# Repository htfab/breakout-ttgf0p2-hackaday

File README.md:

# Tiny Tapeout GF 0p2 Hackaday PCB

<!--&emsp;
-->

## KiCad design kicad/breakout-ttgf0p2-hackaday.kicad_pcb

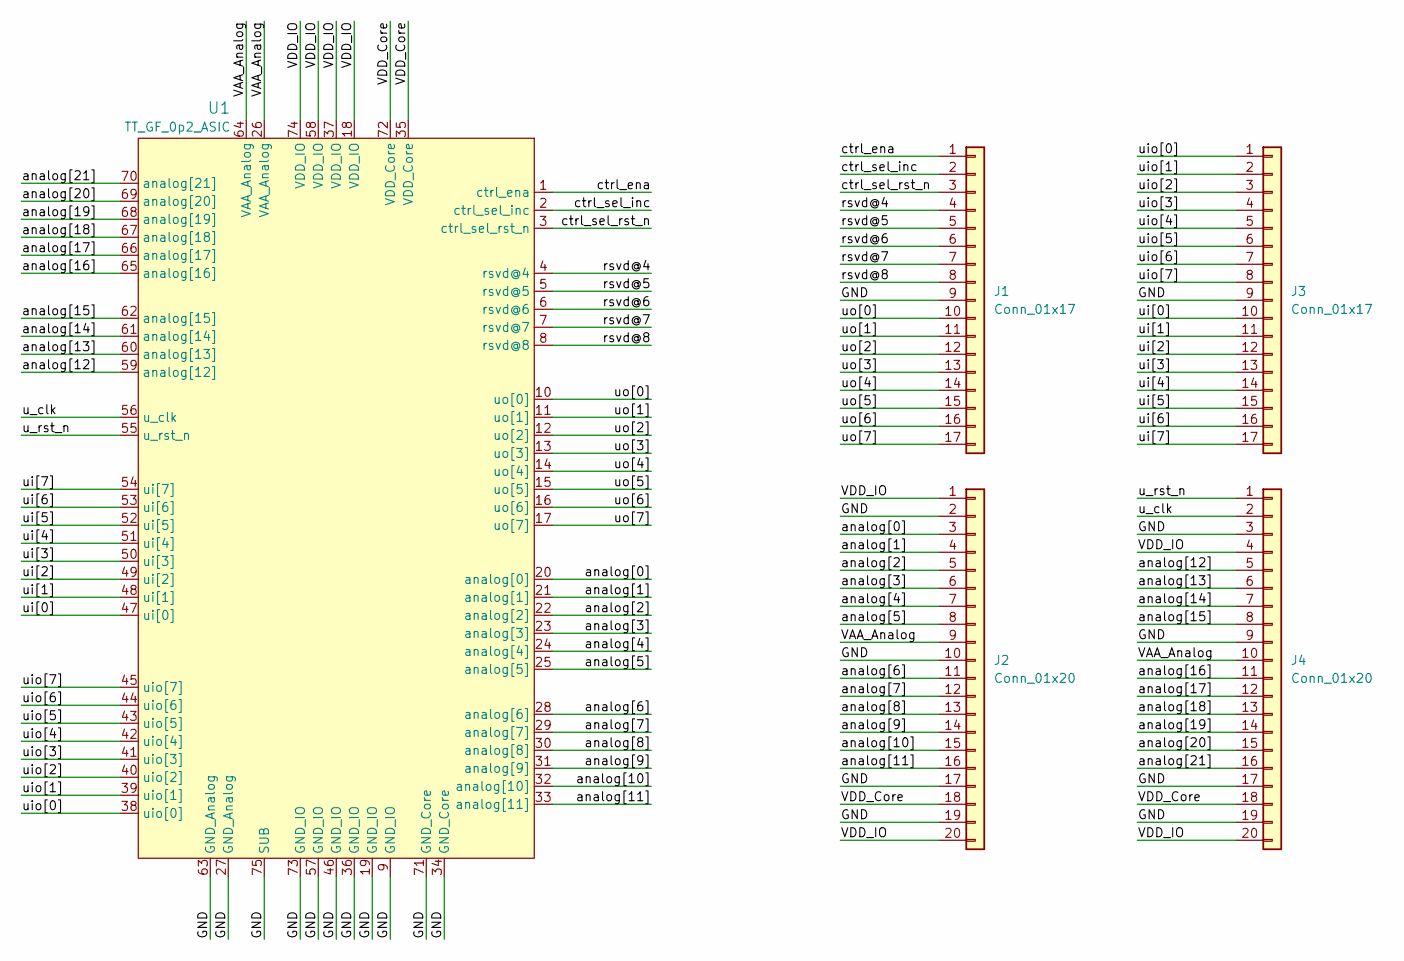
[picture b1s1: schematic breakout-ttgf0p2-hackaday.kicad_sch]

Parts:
J1, J3: Conn_01x17; PinHeader_1x17_P2.54mm_Castellated
J2, J4: Conn_01x20; PinHeader_1x20_P2.54mm_Castellated
U1: TT_GF_0p2_ASIC; ttgf0p2_cob

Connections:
/GND: J1.9, J2.2, J2.10, J2.17, J2.19, J3.9, J4.3, J4.9, J4.17, J4.19, U1.9 (GND_IO), U1.19 (GND_IO), U1.27 (GND_Analog), U1.34 (GND_Core), U1.36 (GND_IO), U1.46 (GND_IO), U1.57 (GND_IO), U1.63 (GND_Analog), U1.71 (GND_Core), U1.73 (GND_IO), U1.75 (SUB)
/VAA_Analog: J2.9, J4.10, U1.26 (VAA_Analog), U1.64 (VAA_Analog)
/VDD_Core: J2.18, J4.18, U1.35 (VDD_Core), U1.72 (VDD_Core)
/VDD_IO: J2.1, J2.20, J4.4, J4.20, U1.18 (VDD_IO), U1.37 (VDD_IO), U1.58 (VDD_IO), U1.74 (VDD_IO)
/analog[0]: J2.3, U1.20 (analog[0])
/analog[1]: J2.4, U1.21 (analog[1])
/analog[2]: J2.5, U1.22 (analog[2])
/analog[3]: J2.6, U1.23 (analog[3])
/analog[4]: J2.7, U1.24 (analog[4])
/analog[5]: J2.8, U1.25 (analog[5])
/analog[6]: J2.11, U1.28 (analog[6])
/analog[7]: J2.12, U1.29 (analog[7])
/analog[8]: J2.13, U1.30 (analog[8])
/analog[9]: J2.14, U1.31 (analog[9])
/analog[10]: J2.15, U1.32 (analog[10])
/analog[11]: J2.16, U1.33 (analog[11])
/analog[12]: J4.5, U1.59 (analog[12])
/analog[13]: J4.6, U1.60 (analog[13])
/analog[14]: J4.7, U1.61 (analog[14])
/analog[15]: J4.8, U1.62 (analog[15])
/analog[16]: J4.11, U1.65 (analog[16])
/analog[17]: J4.12, U1.66 (analog[17])
/analog[18]: J4.13, U1.67 (analog[18])
/analog[19]: J4.14, U1.68 (analog[19])
/analog[20]: J4.15, U1.69 (analog[20])
/analog[21]: J4.16, U1.70 (analog[21])
/ctrl_ena: J1.1, U1.1 (ctrl_ena)
/ctrl_sel_inc: J1.2, U1.2 (ctrl_sel_inc)
/ctrl_sel_rst_n: J1.3, U1.3 (ctrl_sel_rst_n)
/rsvd@4: J1.4, U1.4 (rsvd@4)
/rsvd@5: J1.5, U1.5 (rsvd@5)
/rsvd@6: J1.6, U1.6 (rsvd@6)
/rsvd@7: J1.7, U1.7 (rsvd@7)
/rsvd@8: J1.8, U1.8 (rsvd@8)
/u_clk: J4.2, U1.56 (u_clk)
/u_rst_n: J4.1, U1.55 (u_rst_n)
/ui[0]: J3.10, U1.47 (ui[0])
/ui[1]: J3.11, U1.48 (ui[1])
/ui[2]: J3.12, U1.49 (ui[2])
/ui[3]: J3.13, U1.50 (ui[3])
/ui[4]: J3.14, U1.51 (ui[4])
/ui[5]: J3.15, U1.52 (ui[5])
/ui[6]: J3.16, U1.53 (ui[6])
/ui[7]: J3.17, U1.54 (ui[7])
/uio[0]: J3.1, U1.38 (uio[0])
/uio[1]: J3.2, U1.39 (uio[1])
/uio[2]: J3.3, U1.40 (uio[2])
/uio[3]: J3.4, U1.41 (uio[3])
/uio[4]: J3.5, U1.42 (uio[4])
/uio[5]: J3.6, U1.43 (uio[5])
/uio[6]: J3.7, U1.44 (uio[6])
/uio[7]: J3.8, U1.45 (uio[7])
/uo[0]: J1.10, U1.10 (uo[0])
/uo[1]: J1.11, U1.11 (uo[1])
/uo[2]: J1.12, U1.12 (uo[2])
/uo[3]: J1.13, U1.13 (uo[3])
/uo[4]: J1.14, U1.14 (uo[4])
/uo[5]: J1.15, U1.15 (uo[5])
/uo[6]: J1.16, U1.16 (uo[6])
/uo[7]: J1.17, U1.17 (uo[7])

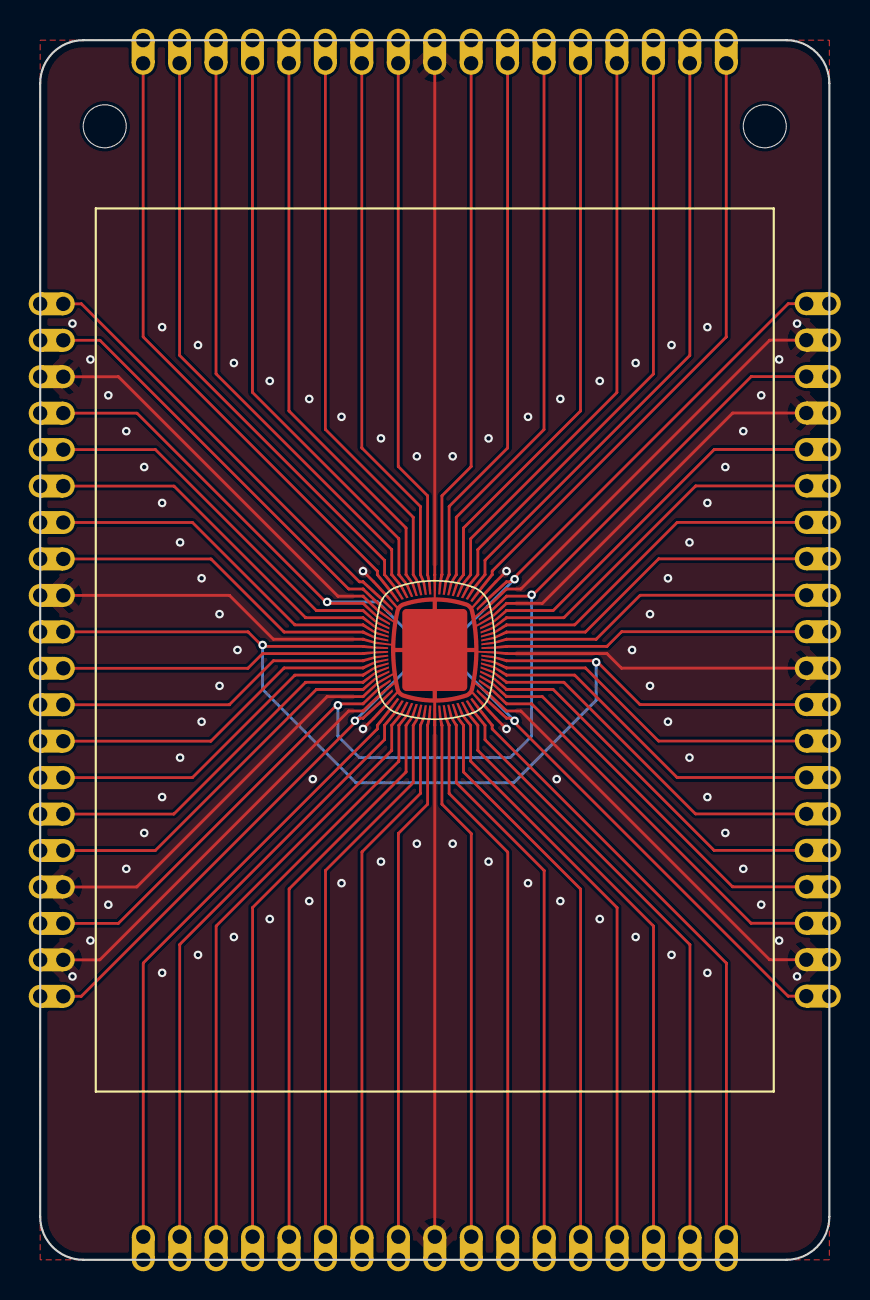
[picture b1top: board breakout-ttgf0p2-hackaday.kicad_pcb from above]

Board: 2 copper layers, 55.0 x 85.0 mm, 5 parts (0 on the bottom side), 60 nets.

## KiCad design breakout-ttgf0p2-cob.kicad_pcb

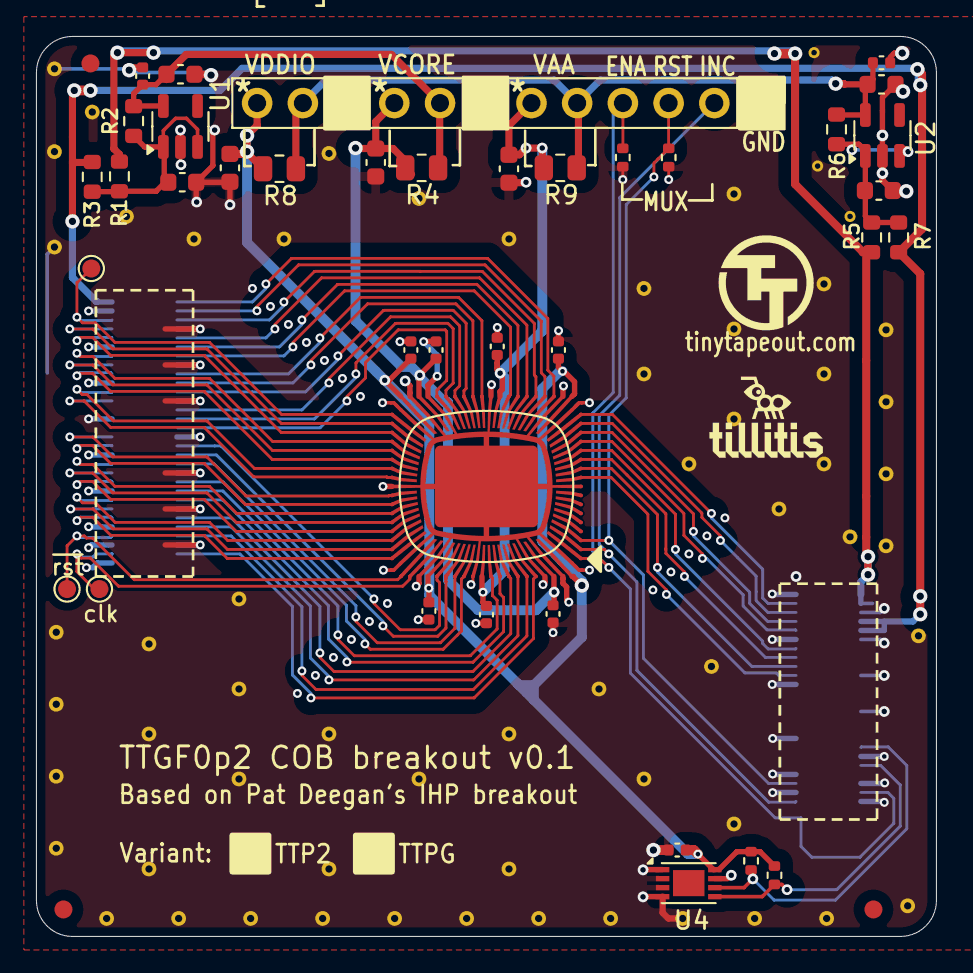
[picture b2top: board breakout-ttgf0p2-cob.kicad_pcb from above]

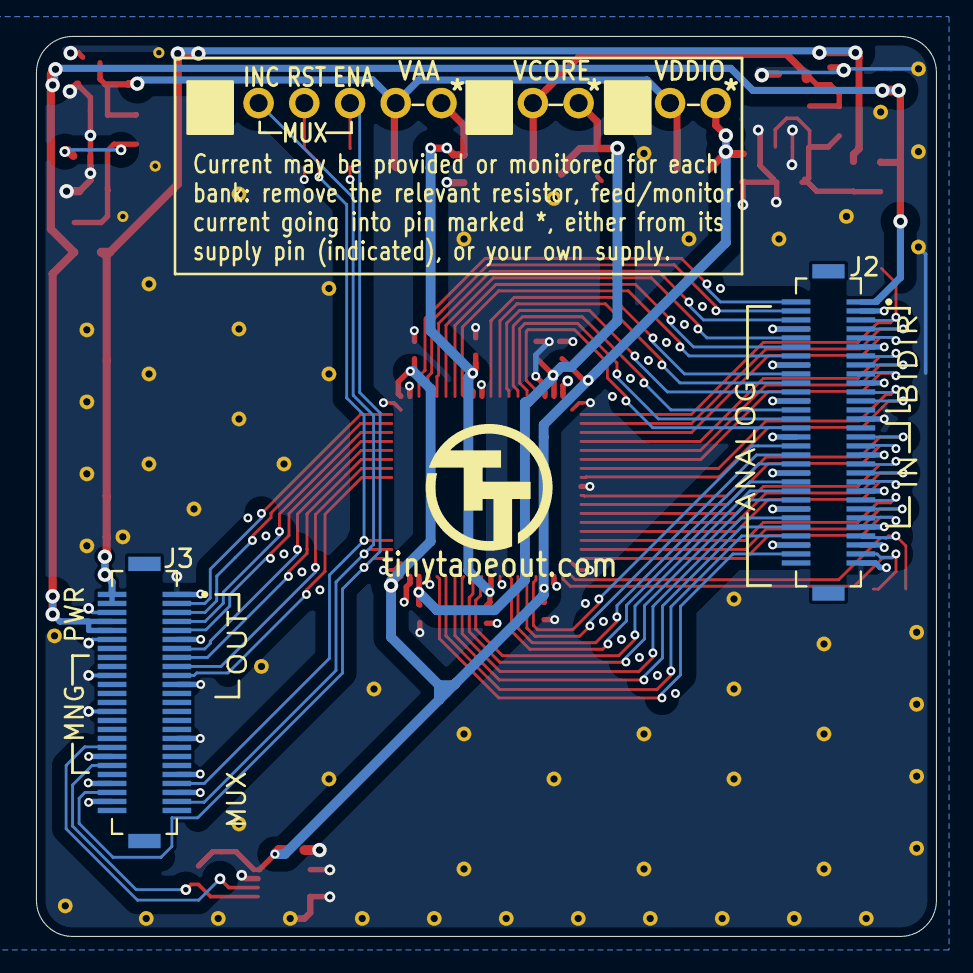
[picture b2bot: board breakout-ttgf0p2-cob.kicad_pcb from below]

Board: 4 copper layers, 50.0 x 50.0 mm, 106 parts (3 on the bottom side), 63 nets.

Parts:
C1, C2, C4, C5, C6, C8, C9: 10uF; C_0603_1608Metric
C3, C7, C15: 100nF; C_0402_1005Metric
C10, C11, C12, C13, C14, C16, C17: 1u; C_0402_1005Metric
FID1, FID2, FID3: Fiducial; Fiducial_1mm_Mask2mm
J1: Conn_01x12; PinHeader_1x12_P2.54mm_Vertical
J2: DF12NB-60DS-0.5V_51; HRS_DF12NB-60DS-0.5V_51
J3: DF12NB-50DS-0.5V_51; HRS_DF12NB-50DS-0.5V_51
R1, R2, R3, R5, R6, R7: 0; R_0603_1608Metric
R4, R8, R9: 0; R_0805_2012Metric
R10, R11: 1k; R_0402_1005Metric
R12, R13: 2k; R_0402_1005Metric
STITCH01, STITCH02, STITCH03, STITCH04, STITCH05, STITCH06, STITCH07, STITCH08, STITCH09, STITCH10, STITCH11, STITCH12, STITCH13, STITCH14, STITCH15, STITCH16, STITCH17, STITCH18, STITCH19, STITCH20, STITCH21, STITCH22, STITCH23, STITCH24, STITCH25, STITCH26, STITCH27, STITCH28, STITCH29, STITCH30, STITCH31, STITCH32, STITCH33, STITCH34, STITCH35, STITCH36, STITCH37, STITCH38, STITCH39, STITCH40, STITCH41, STITCH42, STITCH43, STITCH44, STITCH45, STITCH46, STITCH47, STITCH48, STITCH49, STITCH50, STITCH51, STITCH52, STITCH53, STITCH54, STITCH55, STITCH56, STITCH57: StitchingVia-0.4mmDrill
STITCHSM01, STITCHSM02, STITCHSM03: StitchingVia-0.3mm
TILL1: Tillitis_logo; tillitis_logo
TP1, TP2, TP3: TestPoint; TestPoint_Pad_D1.0mm
TTLOGO1, TTLOGO1#2: TT_logo
U1, U2: AP2112K-3.3; SOT-23-5
U3: TT_GF_0p2_ASIC; ttgf0p2_cob
U4: 24LC02; DFN-8-1EP_3x2mm_P0.5mm_EP1.75x1.45mm

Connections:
+3V3: J2.1, J3.8, J3.10, R3.1, R7.1
+5V: J3.2, J3.4, R1.1, R5.1
/VCOREIN: C1.1, R1.2, R2.1, R3.2, U1.1 (VIN), U1.3 (EN)
/VDIN: C5.1, R5.2, R6.1, R7.2, U2.1 (VIN), U2.3 (EN)
/an0: J2.2, U3.20 (analog[0])
/an1: J2.4, U3.21 (analog[1])
/an2: J2.6, U3.22 (analog[2])
/an3: J2.10, U3.23 (analog[3])
/an4: J2.12, U3.24 (analog[4])
/an5: J2.14, U3.25 (analog[5])
/an6: J2.18, U3.28 (analog[6])
/an7: J2.20, U3.29 (analog[7])
/an8: J2.22, U3.30 (analog[8])
/an9: J2.26, U3.31 (analog[9])
/an10: J2.28, U3.32 (analog[10])
/an11: J2.30, U3.33 (analog[11])
/an12: J2.34, U3.59 (analog[12])
/an13: J2.36, U3.60 (analog[13])
/an14: J2.38, U3.61 (analog[14])
/an15: J2.42, U3.62 (analog[15])
/an16: J2.44, U3.65 (analog[16])
/an17: J2.46, U3.66 (analog[17])
/an18: J2.50, U3.67 (analog[18])
/an19: J2.52, U3.68 (analog[19])
/an20: J2.54, U3.69 (analog[20])
/an21: J2.58, U3.70 (analog[21])
/enable: J1.4, J3.46, R11.1, U3.1 (ctrl_ena)
/increment: J1.2, J3.47, U3.2 (ctrl_sel_inc)
/mngIO1: J3.40, R12.2, U4.5 (SDA)
/mngIO2: J3.36, R13.2, U4.6 (SCL)
/p_clk: J2.57, TP1.1, U3.56 (u_clk)
/rst_n: J1.3, J3.43, R10.1, U3.3 (ctrl_sel_rst_n)
/uin0: J2.31, U3.47 (ui[0])
/uin1: J2.33, U3.48 (ui[1])
/uin2: J2.37, U3.49 (ui[2])
/uin3: J2.39, U3.50 (ui[3])
/uin4: J2.41, U3.51 (ui[4])
/uin5: J2.45, U3.52 (ui[5])
/uin6: J2.47, U3.53 (ui[6])
/uin7: J2.49, U3.54 (ui[7])
/uio0: J2.5, TP3.1, U3.38 (uio[0])
/uio1: J2.7, U3.39 (uio[1])
/uio2: J2.9, U3.40 (uio[2])
/uio3: J2.13, U3.41 (uio[3])
/uio4: J2.15, U3.42 (uio[4])
/uio5: J2.17, U3.43 (uio[5])
/uio6: J2.21, U3.44 (uio[6])
/uio7: J2.23, U3.45 (uio[7])
/uout0: J3.19, U3.10 (uo[0])
/uout1: J3.17, U3.11 (uo[1])
/uout2: J3.15, U3.12 (uo[2])
/uout3: J3.13, U3.13 (uo[3])
/uout4: J3.9, U3.14 (uo[4])
/uout5: J3.7, U3.15 (uo[5])
/uout6: J3.5, U3.16 (uo[6])
/uout7: J3.3, U3.17 (uo[7])
/~p_rst: J2.53, TP2.1, U3.55 (u_rst_n)
GND: C1.2, C2.2, C3.2, C4.2, C5.2, C6.2, C7.2, C8.2, C9.2, C10.2, C11.2, C12.2, C13.2, C14.2, C15.1, C16.2, C17.2, J1.1, J1.7, J1.10, J2.3, J2.8, J2.11, J2.16, J2.19, J2.24, J2.27, J2.32, J2.35, J2.40, J2.43, J2.48, J2.51, J2.55, J2.56, J2.59, J3.1, J3.6, J3.11, J3.12, J3.20, J3.21, J3.28, J3.33, J3.38, J3.41, J3.44, J3.45, J3.48, R10.2, R11.2, STITCH01.1, STITCH02.1, STITCH03.1, STITCH04.1, STITCH05.1, STITCH06.1, STITCH07.1, STITCH08.1, STITCH09.1, STITCH10.1, STITCH11.1, STITCH12.1, STITCH13.1, STITCH14.1, STITCH15.1, STITCH16.1, STITCH17.1, STITCH18.1, STITCH19.1, STITCH20.1, STITCH21.1, STITCH22.1, STITCH23.1, STITCH24.1, STITCH25.1, STITCH26.1, STITCH27.1, STITCH28.1, STITCH29.1, STITCH30.1, STITCH31.1, STITCH32.1, STITCH33.1, STITCH34.1, STITCH35.1, STITCH36.1, STITCH37.1, STITCH38.1, STITCH39.1, STITCH40.1, STITCH41.1, STITCH42.1, STITCH43.1, STITCH44.1, STITCH45.1, STITCH46.1, STITCH47.1, STITCH48.1, STITCH49.1, STITCH50.1, STITCH51.1, STITCH52.1, STITCH53.1, STITCH54.1, STITCH55.1, STITCH56.1, STITCH57.1, STITCHSM01.1, STITCHSM02.1, STITCHSM03.1, U1.2 (GND), U2.2 (GND), U3.9 (GND_IO), U3.19 (GND_IO), U3.27 (GND_Analog), U3.34 (GND_Core), U3.36 (GND_IO), U3.46 (GND_IO), U3.57 (GND_IO), U3.63 (GND_Analog), U3.71 (GND_Core), U3.73 (GND_IO), U3.75 (SUB), U4.1 (A0), U4.2 (A1), U4.3 (A2), U4.4 (GND), U4.7 (WP)
VAA: C8.1, C16.1, C17.1, J1.6, R9.2, U3.26 (VAA_Analog), U3.64 (VAA_Analog)
VCORE_{REG}: C2.1, C3.1, J1.8, R2.2, R4.1, U1.5 (VOUT)
VDD_{CORE}: C4.1, C13.1, C14.1, J1.9, R4.2, U3.35 (VDD_Core), U3.72 (VDD_Core)
VDD_{IO}: C9.1, C10.1, C11.1, C12.1, C15.2, J1.12, R8.2, R12.1, R13.1, U3.18 (VDD_IO), U3.37 (VDD_IO), U3.58 (VDD_IO), U3.74 (VDD_IO), U4.8 (VCC)
VIO_{REG}: C6.1, C7.1, J1.5, J1.11, R6.2, R8.1, R9.1, U2.5 (VOUT)

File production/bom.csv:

Designator,Footprint,Quantity,Value,LCSC Part #
"C1, C2, C5, C6",0603,4,10uF,
"C10, C11, C12, C13, C14, C16, C17",0402,7,1u,CL05A105KO5NNNC
"C15, C3, C7",0402,3,100nF,C100072
"C4, C8, C9",0603,3,10uF,C5673
J1,PinHeader_1x12_P2.54mm_Vertical,1,Conn_01x12,
J2,HRS_DF12NB-60DS-0.5V_51,1,DF12NB-60DS-0.5V_51,C5137127
J3,HRS_DF12NB-50DS-0.5V_51,1,DF12NB-50DS-0.5V_51,C2858672
"R1, R2, R5",0603,3,0,CRG0603ZR
"R10, R11",0402,2,1k,C11702
"R12, R13",0402,2,2k,RC0402FR-072KL
"R3, R6, R7",0603,3,0,C95177
"R4, R8, R9",0805,3,0,C4143065
"U1, U2",SOT-23-5,2,AP2112K-3.3,C23380830
U3,ttgf0p2_cob,1,TT_GF_0p2_ASIC,
U4,DFN-8-1EP_3x2mm_P0.5mm_EP1.75x1.45mm,1,24LC02,C612280

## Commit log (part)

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2026-03-17 initial version based on Pat's breakout-ihp-qfn
2026-03-17 add wiring
2026-03-18 remove stray piece of wire
2026-03-19 add tillitis logo
2026-03-19 implement fixes suggested by Sylvain
2026-03-19 add production files
2026-03-19 update metadata
2026-03-19 add silkscreen for marking TTP2 vs TTPG
2026-04-15 initial hackaday design
2026-04-15 move kicad files into a subdir
2026-04-15 increase back-side spacing & remove fill
2026-04-15 add preliminary silkscreen & easyeda files
2026-04-15 remove stale README & deploy script
2026-04-15 fix some copper shapes
2026-04-16 remove castellated pads
2026-04-16 apply silkscreen design v2
2026-04-16 use faux gold instead of ENIG+FR4 stripes for top silk
